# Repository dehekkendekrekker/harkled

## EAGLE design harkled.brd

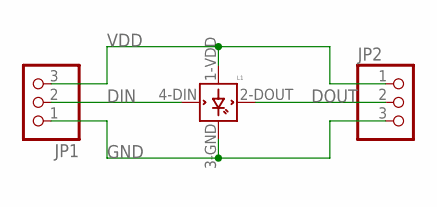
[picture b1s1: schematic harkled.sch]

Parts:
JP1, JP2: PINHD-1X3; 1X03
L1: WS2812B

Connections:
DIN: JP1.2, L1.4-DIN (DIN)
DOUT: JP2.2, L1.2-DOUT (DOUT)
GND: JP1.1, JP2.3, L1.3-GND (GND)
VDD: JP1.3, JP2.1, L1.1-VDD (VDD)

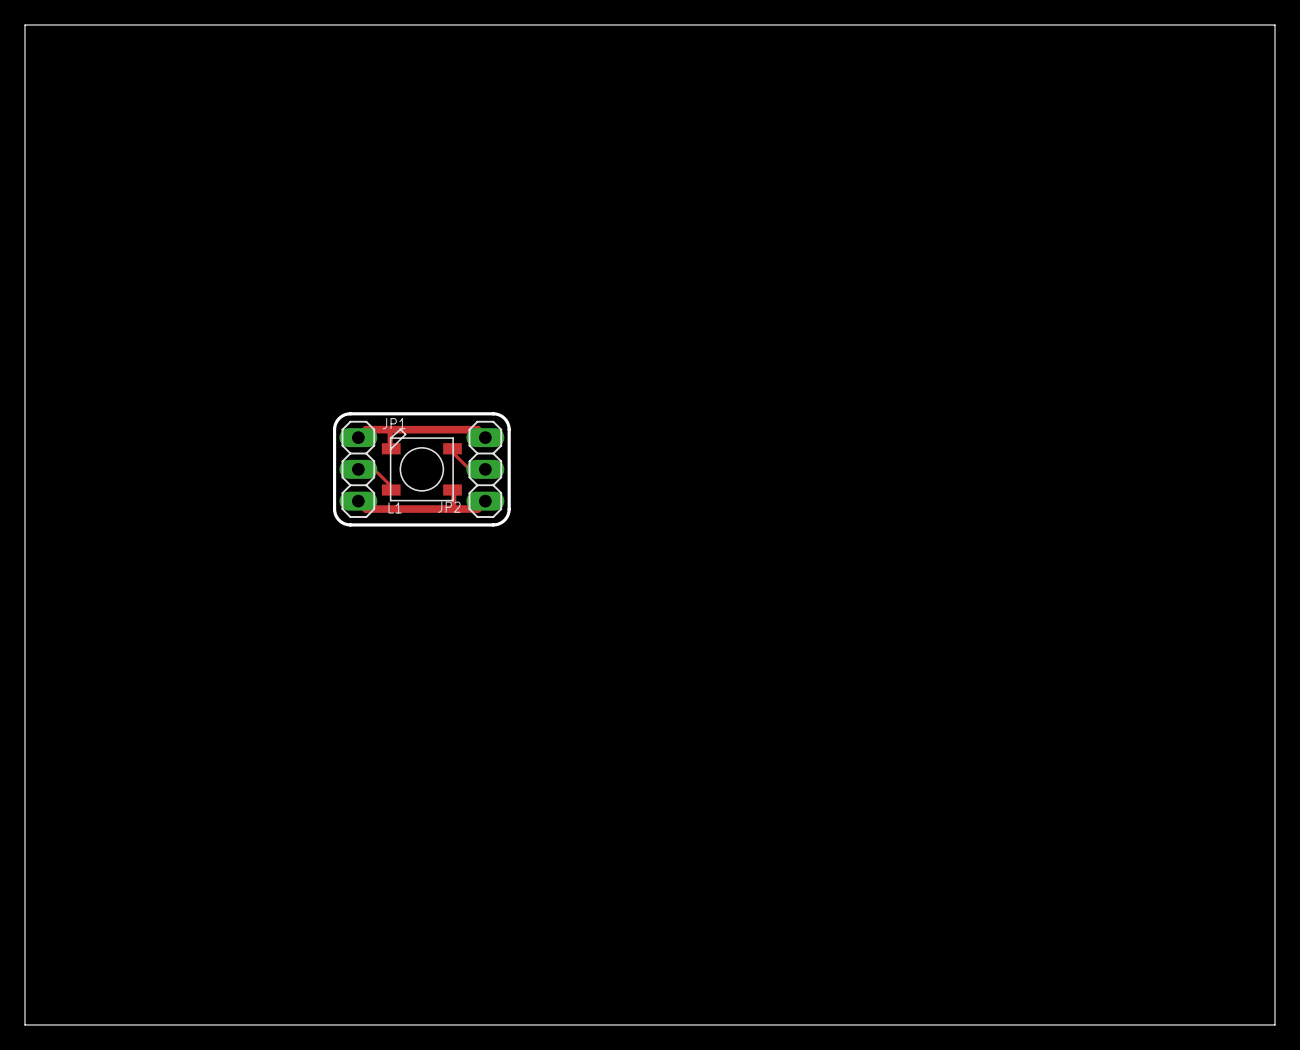
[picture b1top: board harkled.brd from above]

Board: 2 copper layers, 100.0 x 80.0 mm, 3 parts (0 on the bottom side), 4 nets.

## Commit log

2015-01-31 Initials commit
